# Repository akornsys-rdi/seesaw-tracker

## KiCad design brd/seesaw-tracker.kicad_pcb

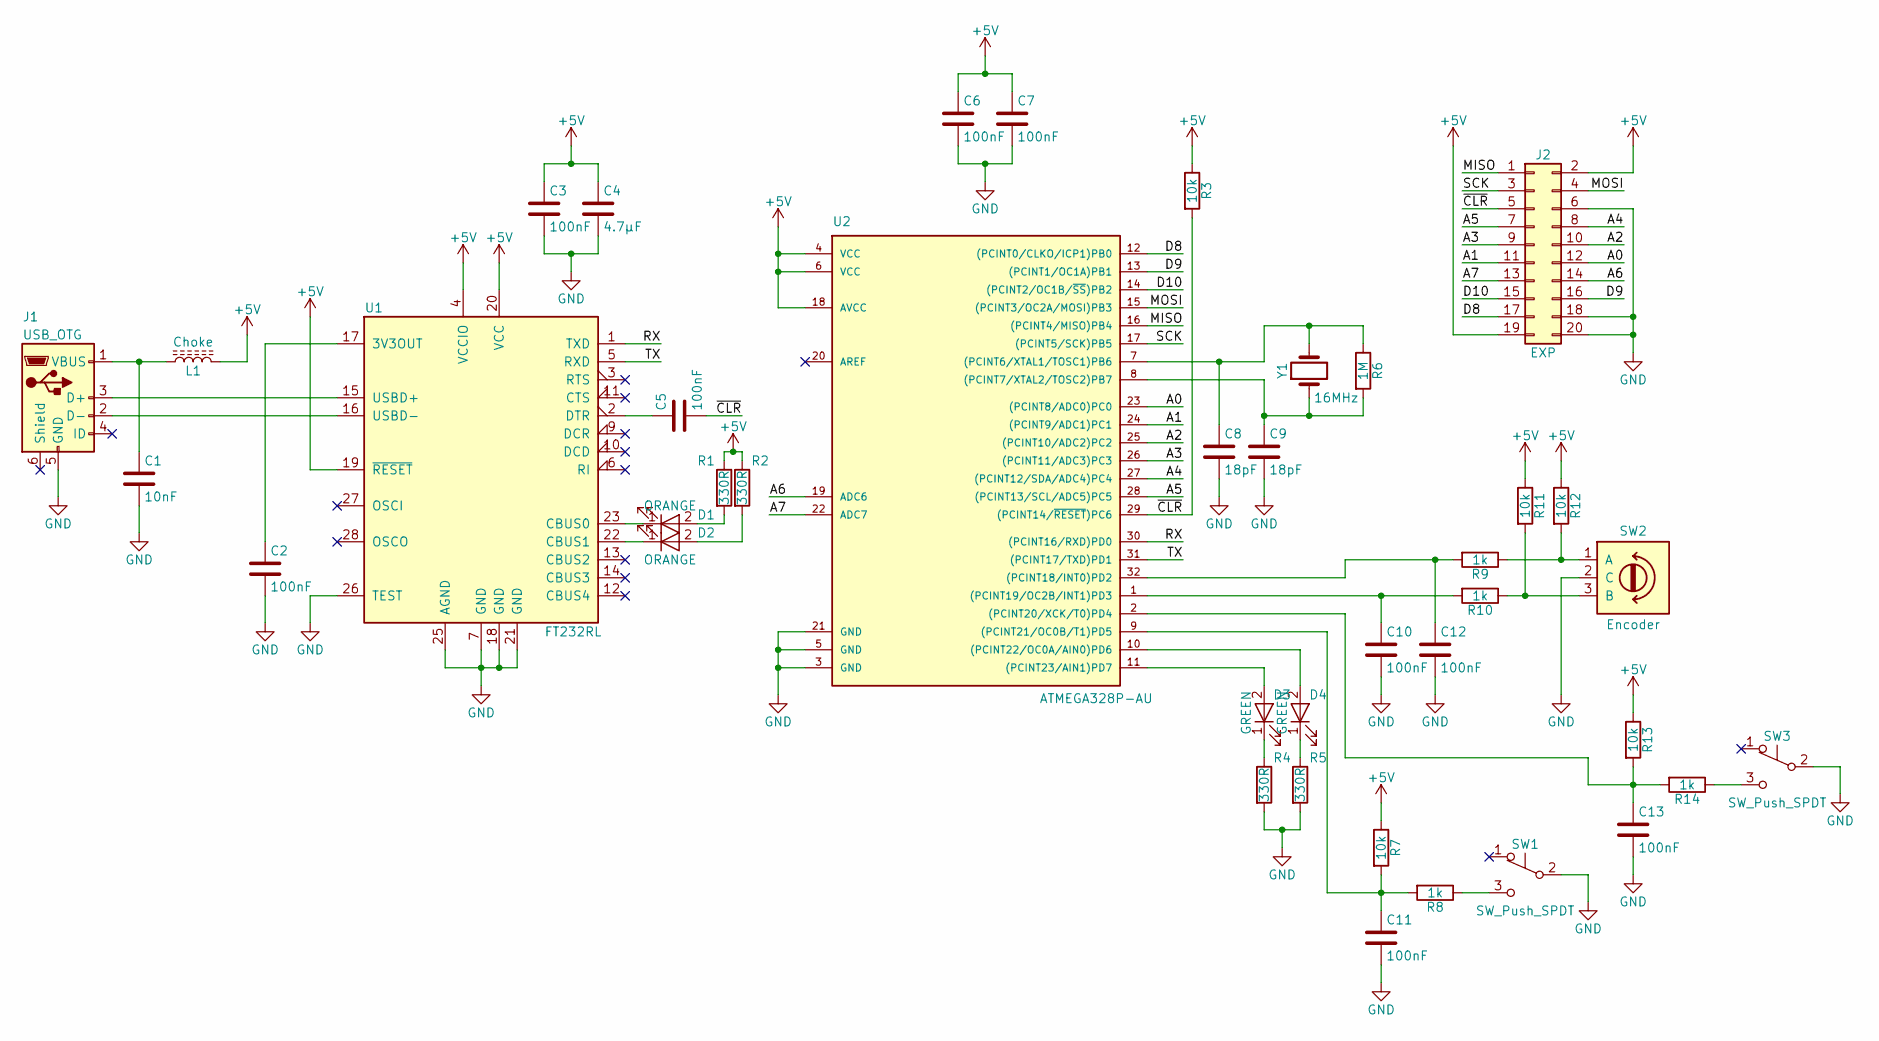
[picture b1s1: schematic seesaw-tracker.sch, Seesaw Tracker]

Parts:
C1: 10nF; C_0805; Manufacturer Part Number C0805C103K1RACTU
C2, C3, C5, C6, C7, C10, C11, C12, C13: 100nF; C_0805; Manufacturer Part Number C0805C104J5RACTU
C4: 4.7µF; C_0805; Manufacturer Part Number C0805C475K8PACTU
C8, C9: 18pF; C_0805; Manufacturer Part Number C0805C180J5GAC
D1, D2: ORANGE; LED_0805; Manufacturer Part Number LO R976-PS-1
D3, D4: GREEN; LED_0805; Manufacturer Part Number LG R971-KN-1
J1: USB_OTG; USB_Mini-B; Manufacturer Part Number UJ2-MBH-1-SMT-TR
J2: EXP; Pin_Header_Straight_2x10_Pitch2.54mm
L1: Choke; L_0805_HandSoldering; Manufacturer Part Number BLM21PG331SN1D
R1, R2, R4, R5: 330R; R_0805_HandSoldering; Manufacturer Part Number CR0805-JW-331ELF
R3, R7, R11, R12, R13: 10k; R_0805_HandSoldering; Manufacturer Part Number CR0805-JW-103ELF
R6: 1M; R_0805_HandSoldering; Manufacturer Part Number CR0805-JW-105ELF
R8, R10, R14: 1k; R_0805_HandSoldering; Manufacturer Part Number CR0805-JW-102ELF
R9: 1k; R_0805_HandSoldering; Manufacture Part Number CR0805-JW-102ELF
SW1, SW3: SW_Push_SPDT; ZM90; Manufacturer Part Number ZM90G20F01
SW2: Encoder; PEC12R; Manufacturer Part Number PEC12R-4222F-N0024
U1: FT232RL; SSOP-28_5.3x10.2mm_Pitch0.65mm; Manufacturer Part Number FT232RL-REEL
U2: ATMEGA328P-AU; TQFP-32_7x7mm_Pitch0.8mm; Manufacturer Part Number ATMEGA328P-AU
Y1: 16MHz; Crystal_SMD_HC49-SD; Manufacturer Part Number ABLS-16.000MHZ-B4-T

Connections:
+5V: C3.1, C4.1, C6.1, C7.1, J2.2, J2.19, L1.2, R1.1, R2.1, R3.1, R7.1, R11.1, R12.1, R13.1, U1.4 (VCCIO), U1.19 (~RESET~), U1.20 (VCC), U2.4 (VCC), U2.6 (VCC), U2.18 (AVCC)
/A0: J2.12, U2.23 ((PCINT8/ADC0)PC0)
/A1: J2.11, U2.24 ((PCINT9/ADC1)PC1)
/A2: J2.10, U2.25 ((PCINT10/ADC2)PC2)
/A3: J2.9, U2.26 ((PCINT11/ADC3)PC3)
/A4: J2.8, U2.27 ((PCINT12/SDA/ADC4)PC4)
/A5: J2.7, U2.28 ((PCINT13/SCL/ADC5)PC5)
/A6: J2.14, U2.19 (ADC6)
/A7: J2.13, U2.22 (ADC7)
/D8: J2.17, U2.12 ((PCINT0/CLKO/ICP1)PB0)
/D9: J2.16, U2.13 ((PCINT1/OC1A)PB1)
/D10: J2.15, U2.14 ((PCINT2/OC1B/~SS~)PB2)
/MISO: J2.1, U2.16 ((PCINT4/MISO)PB4)
/MOSI: J2.4, U2.15 ((PCINT3/OC2A/MOSI)PB3)
/RX: U1.1 (TXD), U2.30 ((PCINT16/RXD)PD0)
/SCK: J2.3, U2.17 ((PCINT5/SCK)PB5)
/TX: U1.5 (RXD), U2.31 ((PCINT17/TXD)PD1)
/~CLR: C5.2, J2.5, R3.2, U2.29 ((PCINT14/~RESET~)PC6)
GND: C1.2, C2.2, C3.2, C4.2, C6.2, C7.2, C8.2, C9.2, C10.2, C11.2, C12.2, C13.2, J1.5 (GND), J2.6, J2.18, J2.20, R4.2, R5.2, SW1.2 (B), SW2.2 (C), SW3.2 (B), U1.7 (GND), U1.18 (GND), U1.21 (GND), U1.25 (AGND), U1.26 (TEST), U2.3 (GND), U2.5 (GND), U2.21 (GND)
unnamed: C1.1, J1.1 (VBUS), L1.1
unnamed: C2.1, U1.17 (3V3OUT)
unnamed: C5.1, U1.2 (DTR)
unnamed: C8.1, R6.1, U2.7 ((PCINT6/XTAL1/TOSC1)PB6), Y1.2
unnamed: C9.1, R6.2, U2.8 ((PCINT7/XTAL2/TOSC2)PB7), Y1.1
unnamed: C10.1, R10.2, U2.1 ((PCINT19/OC2B/INT1)PD3)
unnamed: C11.1, R7.2, R8.2, U2.9 ((PCINT21/OC0B/T1)PD5)
unnamed: C12.1, R9.2, U2.32 ((PCINT18/INT0)PD2)
unnamed: C13.1, R13.2, R14.2, U2.2 ((PCINT20/XCK/T0)PD4)
unnamed: D1.1 (K), U1.23 (CBUS0)
unnamed: D1.2 (A), R1.2
unnamed: D2.1 (K), U1.22 (CBUS1)
unnamed: D2.2 (A), R2.2
unnamed: D3.1 (K), R4.1
unnamed: D3.2 (A), U2.11 ((PCINT23/AIN1)PD7)
unnamed: D4.1 (K), R5.1
unnamed: D4.2 (A), U2.10 ((PCINT22/OC0A/AIN0)PD6)
unnamed: J1.2 (D-), U1.16 (USBD-)
unnamed: J1.3 (D+), U1.15 (USBD+)
unnamed: R8.1, SW1.3 (C)
unnamed: R10.1, R11.2, SW2.3 (B)
unnamed: R9.1, R12.2, SW2.1 (A)
unnamed: R14.1, SW3.3 (C)

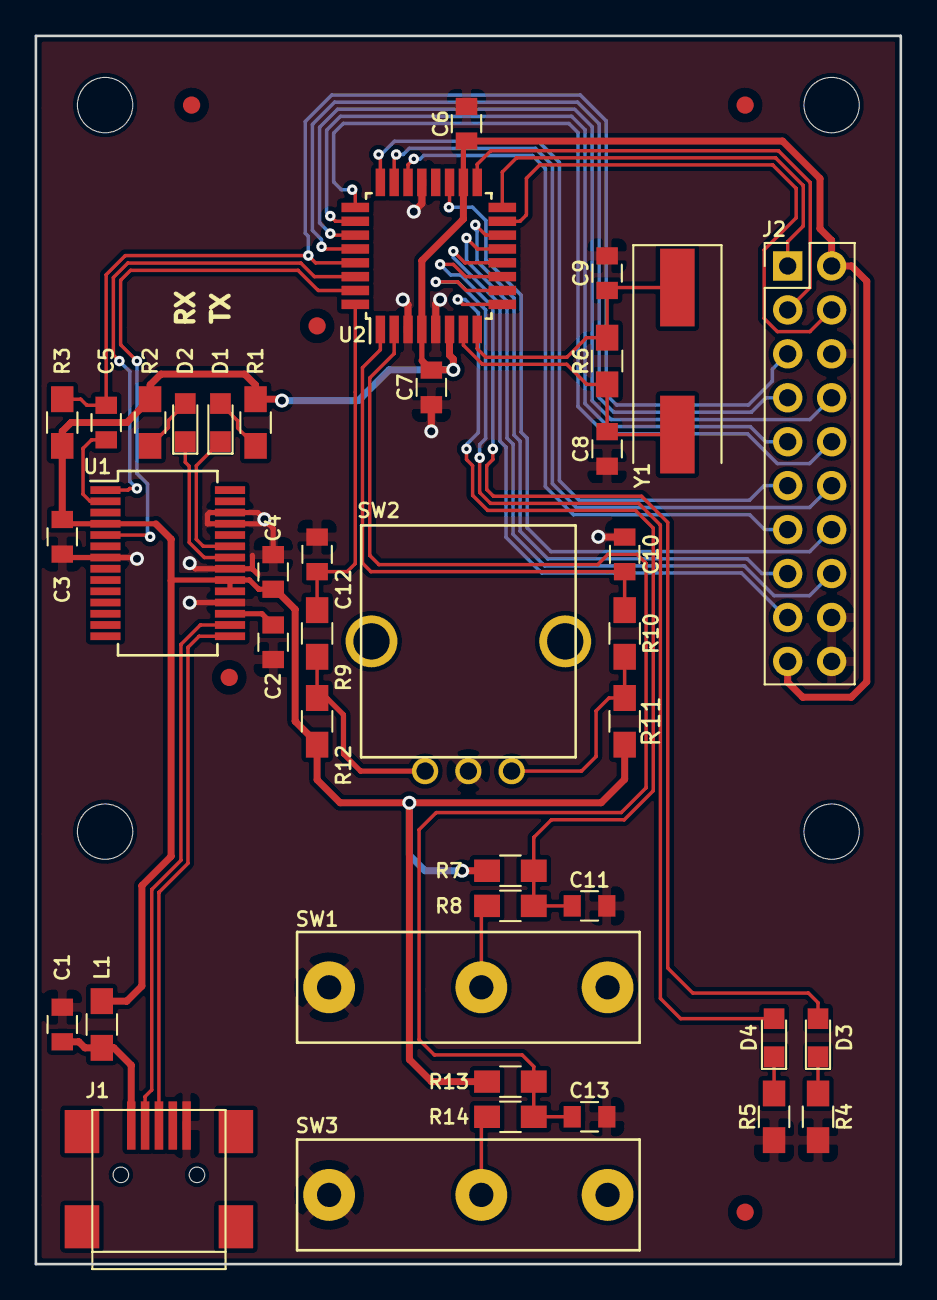
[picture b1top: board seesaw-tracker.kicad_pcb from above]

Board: 2 copper layers, 50.0 x 71.0 mm, 40 parts (0 on the bottom side), 42 nets.

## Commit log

2019-11-30 añadido diseño de pcb
2019-12-06 actualizado diseño pcb
2023-08-11 subidos archivos !WIP

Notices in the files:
brd/seesaw-tracker.kicad_pcb:
Copyright © 2019 kwendenarmo
Released under GNU/GPL 3 License
https://www.gnu.org/licenses/gpl.html
